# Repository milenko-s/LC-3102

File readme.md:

# LibreCube LC-3102 UART Adapter

## About

The UART Adapter is used to connect the UART bus from a microcontroller to the RS232 (serial port) interface of a computer. 

## Authors

- Artur Scholz [artur.scholz@librecube.net]
- Milenko Starcik [-]

## Acknowledgements

- Development supported from National Cheng Kung University (www.ncku.edu.tw) under supervision of Prof. Jiun-Jih Miau and Prof. Jyh-Ching Juang and with the help from students of PACELAB and MECLAB.

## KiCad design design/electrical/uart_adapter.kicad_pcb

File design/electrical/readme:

Note:

This project has originally been designed with non-free proprietary software.
This is against the principle of LibreCube, where we promote the use of free
and open source tools for all our projects and activities.

Therefore the source files have not been included in this repository. If you
have the spare time and interest, feel free to re-engineer design files from
the drawings, using KiCAD.

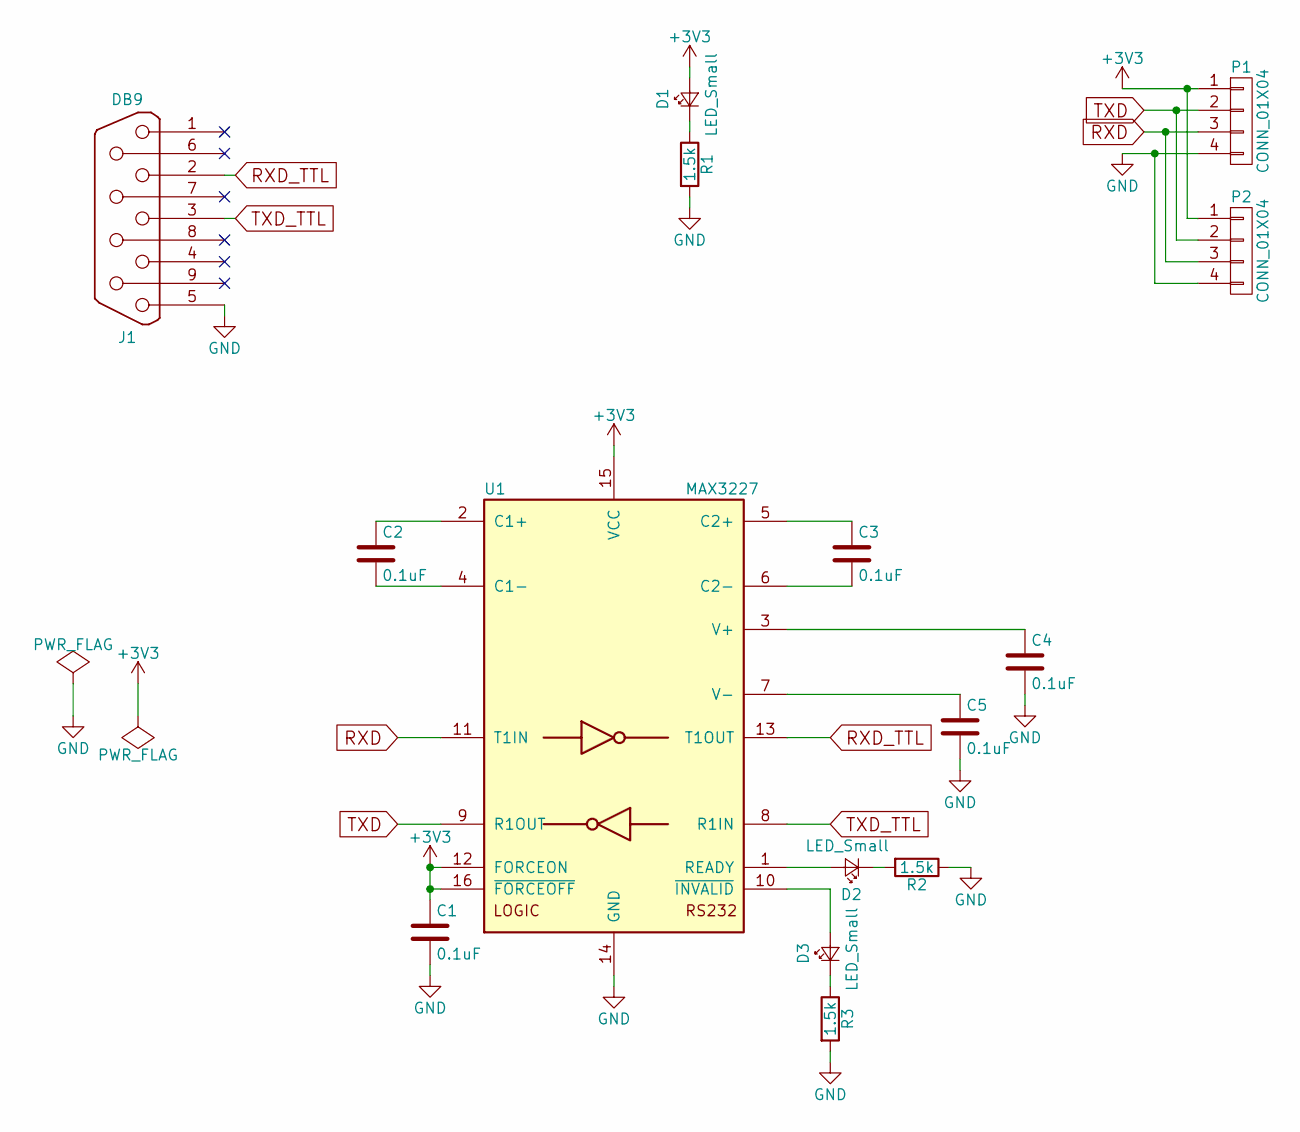
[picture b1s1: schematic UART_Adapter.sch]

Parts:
C1, C2, C3, C4, C5: 0.1uF; C_0805_HandSoldering
D1, D2, D3: LED_Small; LED_0805
J1: DB9; DB9FC
P1, P2: CONN_01X04; Socket_Strip_Straight_1x04
R1, R2, R3: 1.5k; R_0805_HandSoldering
U1: MAX3227; SSOP-16_5.3x6.2mm_Pitch0.65mm

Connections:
+3V3: C1.1, D1.2 (A), P1.1, P2.1, U1.12 (FORCEON), U1.15 (VCC), U1.16 (~FORCEOFF)
GND: C1.2, C4.2, C5.2, J1.5, P1.4, P2.4, R1.2, R2.1, R3.2, U1.14 (GND)
unnamed: C2.1, U1.2 (C1+)
unnamed: C2.2, U1.4 (C1-)
unnamed: C3.1, U1.5 (C2+)
unnamed: C3.2, U1.6 (C2-)
unnamed: C4.1, U1.3 (V+)
unnamed: C5.1, U1.7 (V-)
unnamed: D1.1 (K), R1.1
unnamed: D2.1 (K), R2.2
unnamed: D2.2 (A), U1.1 (READY)
unnamed: D3.1 (K), R3.1
unnamed: D3.2 (A), U1.10 (~INVALID)
RXD: P1.3, P2.3, U1.11 (T1IN)
RXD_TTL: J1.2, U1.13 (T1OUT)
TXD: P1.2, P2.2, U1.9 (R1OUT)
TXD_TTL: J1.3, U1.8 (R1IN)

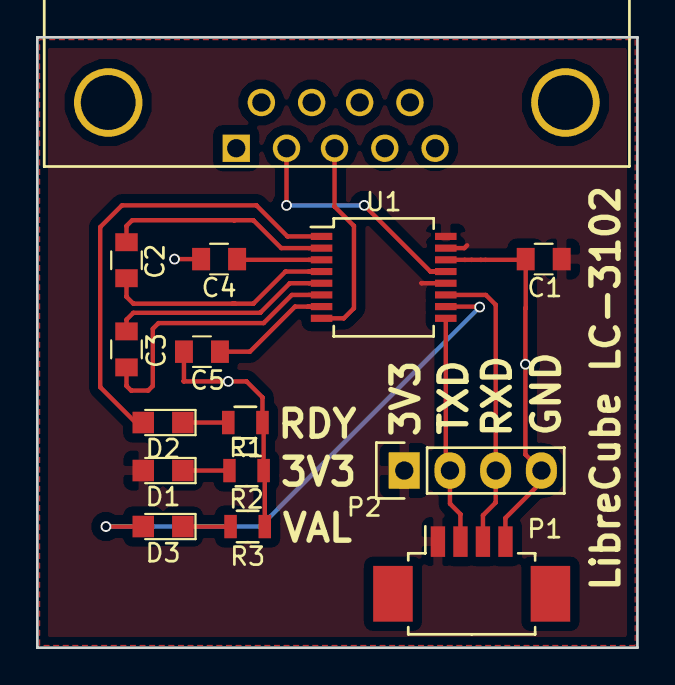
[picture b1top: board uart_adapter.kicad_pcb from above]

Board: 2 copper layers, 33.3 x 33.9 mm, 15 parts (0 on the bottom side), 17 nets.

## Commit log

2016-05-22 mod: remove non-free source files
2017-01-14 Started PCB design
2017-01-16 some cleanup
2017-01-16 Rename UART_Adapter-cache.lib to uart_adapter-cache.lib
2017-01-16 Rename UART_Adapter.sch to uart_adapter.sch
2017-01-16 Rename UART_Adapter.kicad_pcb to uart_adapter.kicad_pcb
2017-01-16 Rename UART_Adapter.net to uart_adapter.net
2017-01-16 Rename UART_Adapter.pro to uart_adapter.pro
2017-01-16 Added Molex connector
2017-01-18 Created power and ground plane
2017-01-20 3D-View in KiCad
2017-01-20 New bom files
2017-01-20 new pdf layer files
2017-01-20 Outline changed
2017-01-20 New gerber files
